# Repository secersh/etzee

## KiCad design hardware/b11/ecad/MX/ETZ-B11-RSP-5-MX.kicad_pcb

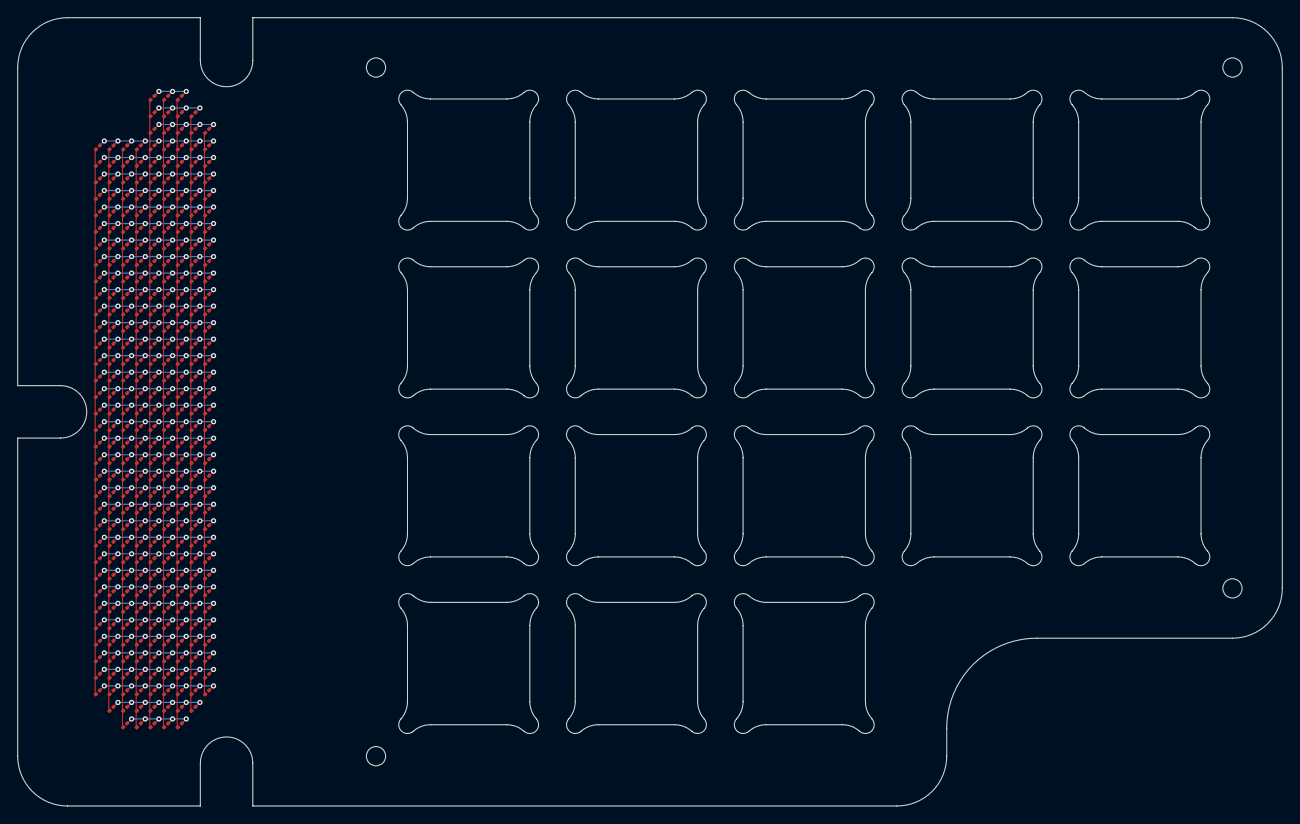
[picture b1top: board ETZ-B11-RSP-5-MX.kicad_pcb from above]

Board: 2 copper layers, 144.7 x 90.2 mm, 330 parts (0 on the bottom side), 48 nets.

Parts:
D1, D2, D3, D4, D5, D6, D7, D8, D9, D10, D11, D12, D13, D14, D15, D16, D17, D18, D19, D20, D21, D22, D23, D24, D25, D26, D27, D28, D29, D30, D31, D32, D33, D34, D35, D36, D37, D38, D39, D40, D41, D42, D43, D44, D45, D46, D47, D48, D49, D50, D51, D52, D53, D54, D55, D56, D57, D58, D59, D60, D61, D62, D63, D64, D65, D66, D67, D68, D69, D70, D71, D72, D73, D74, D75, D76, D77, D78, D79, D80, D81, D82, D83, D84, D85, D86, D87, D88, D89, D90, D91, D92, D93, D94, D95, D96, D97, D98, D99, D100, D101, D102, D103, D104, D105, D106, D107, D108, D109, D110, D111, D112, D113, D114, D115, D116, D117, D118, D119, D120, D121, D122, D123, D124, D125, D126, D127, D128, D129, D130, D131, D132, D133, D134, D135, D136, D137, D138, D139, D140, D141, D142, D143, D144, D145, D146, D147, D148, D149, D150, D151, D152, D153, D154, D155, D156, D157, D158, D159, D160, D161, D162, D163, D164, D165, D166, D167, D168, D169, D170, D171, D172, D173, D174, D175, D176, D177, D178, D179, D180, D181, D182, D183, D184, D185, D186, D187, D188, D189, D190, D191, D192, D193, D194, D195, D196, D197, D198, D199, D200, D201, D202, D203, D204, D205, D206, D207, D208, D209, D210, D211, D212, D213, D214, D215, D216, D217, D218, D219, D220, D221, D222, D223, D224, D225, D226, D227, D228, D229, D230, D231, D232, D233, D234, D235, D236, D237, D238, D239, D240, D241, D242, D243, D244, D245, D246, D247, D248, D249, D250, D251, D252, D253, D254, D255, D256, D257, D258, D259, D260, D261, D262, D263, D264, D265, D266, D267, D268, D269, D270, D271, D272, D273, D274, D275, D276, D277, D278, D279, D280, D281, D282, D283, D284, D285, D286, D287, D288, D289, D290, D291, D292, D293, D294, D295, D296, D297, D298, D299, D300, D301, D302, D303, D304, D305, D306, D307, D308, D309, D310, D311, D312, D313, D314, D315, D316, D317, D318, D319, D320, D321, D322, D323, D324, D325, D326, D327, D328, D329, D330: 0201_LED

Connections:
LED_CS1: D1.1, D2.1, D3.1
LED_CS2: D4.1, D5.1, D6.1, D7.1
LED_CS3: D8.1, D9.1, D10.1, D11.1, D12.1
LED_CS4: D13.1, D14.1, D15.1, D16.1, D17.1, D18.1, D19.1, D20.1, D21.1
LED_CS5: D22.1, D23.1, D24.1, D25.1, D26.1, D27.1, D28.1, D29.1, D30.1
LED_CS6: D31.1, D32.1, D33.1, D34.1, D35.1, D36.1, D37.1, D38.1, D39.1
LED_CS7: D40.1, D41.1, D42.1, D43.1, D44.1, D45.1, D46.1, D47.1, D48.1
LED_CS8: D49.1, D50.1, D51.1, D52.1, D53.1, D54.1, D55.1, D56.1, D57.1
LED_CS9: D58.1, D59.1, D60.1, D61.1, D62.1, D63.1, D64.1, D65.1, D66.1
LED_CS10: D67.1, D68.1, D69.1, D70.1, D71.1, D72.1, D73.1, D74.1, D75.1
LED_CS11: D76.1, D77.1, D78.1, D79.1, D80.1, D81.1, D82.1, D83.1, D84.1
LED_CS12: D85.1, D86.1, D87.1, D88.1, D89.1, D90.1, D91.1, D92.1, D93.1
LED_CS13: D94.1, D95.1, D96.1, D97.1, D98.1, D99.1, D100.1, D101.1, D102.1
LED_CS14: D103.1, D104.1, D105.1, D106.1, D107.1, D108.1, D109.1, D110.1, D111.1
LED_CS15: D112.1, D113.1, D114.1, D115.1, D116.1, D117.1, D118.1, D119.1, D120.1
LED_CS16: D121.1, D122.1, D123.1, D124.1, D125.1, D126.1, D127.1, D128.1, D129.1
LED_CS17: D130.1, D131.1, D132.1, D133.1, D134.1, D135.1, D136.1, D137.1, D138.1
LED_CS18: D139.1, D140.1, D141.1, D142.1, D143.1, D144.1, D145.1, D146.1, D147.1
LED_CS19: D148.1, D149.1, D150.1, D151.1, D152.1, D153.1, D154.1, D155.1, D156.1
LED_CS20: D157.1, D158.1, D159.1, D160.1, D161.1, D162.1, D163.1, D164.1, D165.1
LED_CS21: D166.1, D167.1, D168.1, D169.1, D170.1, D171.1, D172.1, D173.1, D174.1
LED_CS22: D175.1, D176.1, D177.1, D178.1, D179.1, D180.1, D181.1, D182.1, D183.1
LED_CS23: D184.1, D185.1, D186.1, D187.1, D188.1, D189.1, D190.1, D191.1, D192.1
LED_CS24: D193.1, D194.1, D195.1, D196.1, D197.1, D198.1, D199.1, D200.1, D201.1
LED_CS25: D202.1, D203.1, D204.1, D205.1, D206.1, D207.1, D208.1, D209.1, D210.1
LED_CS26: D211.1, D212.1, D213.1, D214.1, D215.1, D216.1, D217.1, D218.1, D219.1
LED_CS27: D220.1, D221.1, D222.1, D223.1, D224.1, D225.1, D226.1, D227.1, D228.1
LED_CS28: D229.1, D230.1, D231.1, D232.1, D233.1, D234.1, D235.1, D236.1, D237.1
LED_CS29: D238.1, D239.1, D240.1, D241.1, D242.1, D243.1, D244.1, D245.1, D246.1
LED_CS30: D247.1, D248.1, D249.1, D250.1, D251.1, D252.1, D253.1, D254.1, D255.1
LED_CS31: D256.1, D257.1, D258.1, D259.1, D260.1, D261.1, D262.1, D263.1, D264.1
LED_CS32: D265.1, D266.1, D267.1, D268.1, D269.1, D270.1, D271.1, D272.1, D273.1
LED_CS33: D274.1, D275.1, D276.1, D277.1, D278.1, D279.1, D280.1, D281.1, D282.1
LED_CS34: D283.1, D284.1, D285.1, D286.1, D287.1, D288.1, D289.1, D290.1, D291.1
LED_CS35: D292.1, D293.1, D294.1, D295.1, D296.1, D297.1, D298.1, D299.1, D300.1
LED_CS36: D301.1, D302.1, D303.1, D304.1, D305.1, D306.1, D307.1, D308.1, D309.1
LED_CS37: D310.1, D311.1, D312.1, D313.1, D314.1, D315.1, D316.1, D317.1, D318.1
LED_CS38: D319.1, D320.1, D321.1, D322.1, D323.1, D324.1, D325.1
LED_CS39: D326.1, D327.1, D328.1, D329.1, D330.1
LED_SW1: D13.2, D22.2, D31.2, D40.2, D49.2, D58.2, D67.2, D76.2, D85.2, D94.2, D103.2, D112.2, D121.2, D130.2, D139.2, D148.2, D157.2, D166.2, D175.2, D184.2, D193.2, D202.2, D211.2, D220.2, D229.2, D238.2, D247.2, D256.2, D265.2, D274.2, D283.2, D292.2, D301.2, D310.2
LED_SW2: D14.2, D23.2, D32.2, D41.2, D50.2, D59.2, D68.2, D77.2, D86.2, D95.2, D104.2, D113.2, D122.2, D131.2, D140.2, D149.2, D158.2, D167.2, D176.2, D185.2, D194.2, D203.2, D212.2, D221.2, D230.2, D239.2, D248.2, D257.2, D266.2, D275.2, D284.2, D293.2, D302.2, D311.2, D319.2
LED_SW3: D15.2, D24.2, D33.2, D42.2, D51.2, D60.2, D69.2, D78.2, D87.2, D96.2, D105.2, D114.2, D123.2, D132.2, D141.2, D150.2, D159.2, D168.2, D177.2, D186.2, D195.2, D204.2, D213.2, D222.2, D231.2, D240.2, D249.2, D258.2, D267.2, D276.2, D285.2, D294.2, D303.2, D312.2, D320.2, D326.2
LED_SW4: D16.2, D25.2, D34.2, D43.2, D52.2, D61.2, D70.2, D79.2, D88.2, D97.2, D106.2, D115.2, D124.2, D133.2, D142.2, D151.2, D160.2, D169.2, D178.2, D187.2, D196.2, D205.2, D214.2, D223.2, D232.2, D241.2, D250.2, D259.2, D268.2, D277.2, D286.2, D295.2, D304.2, D313.2, D321.2, D327.2
LED_SW5: D1.2, D4.2, D8.2, D17.2, D26.2, D35.2, D44.2, D53.2, D62.2, D71.2, D80.2, D89.2, D98.2, D107.2, D116.2, D125.2, D134.2, D143.2, D152.2, D161.2, D170.2, D179.2, D188.2, D197.2, D206.2, D215.2, D224.2, D233.2, D242.2, D251.2, D260.2, D269.2, D278.2, D287.2, D296.2, D305.2, D314.2, D322.2, D328.2
LED_SW6: D2.2, D5.2, D9.2, D18.2, D27.2, D36.2, D45.2, D54.2, D63.2, D72.2, D81.2, D90.2, D99.2, D108.2, D117.2, D126.2, D135.2, D144.2, D153.2, D162.2, D171.2, D180.2, D189.2, D198.2, D207.2, D216.2, D225.2, D234.2, D243.2, D252.2, D261.2, D270.2, D279.2, D288.2, D297.2, D306.2, D315.2, D323.2, D329.2
LED_SW7: D3.2, D6.2, D10.2, D19.2, D28.2, D37.2, D46.2, D55.2, D64.2, D73.2, D82.2, D91.2, D100.2, D109.2, D118.2, D127.2, D136.2, D145.2, D154.2, D163.2, D172.2, D181.2, D190.2, D199.2, D208.2, D217.2, D226.2, D235.2, D244.2, D253.2, D262.2, D271.2, D280.2, D289.2, D298.2, D307.2, D316.2, D324.2, D330.2
LED_SW8: D7.2, D11.2, D20.2, D29.2, D38.2, D47.2, D56.2, D65.2, D74.2, D83.2, D92.2, D101.2, D110.2, D119.2, D128.2, D137.2, D146.2, D155.2, D164.2, D173.2, D182.2, D191.2, D200.2, D209.2, D218.2, D227.2, D236.2, D245.2, D254.2, D263.2, D272.2, D281.2, D290.2, D299.2, D308.2, D317.2, D325.2
LED_SW9: D12.2, D21.2, D30.2, D39.2, D48.2, D57.2, D66.2, D75.2, D84.2, D93.2, D102.2, D111.2, D120.2, D129.2, D138.2, D147.2, D156.2, D165.2, D174.2, D183.2, D192.2, D201.2, D210.2, D219.2, D228.2, D237.2, D246.2, D255.2, D264.2, D273.2, D282.2, D291.2, D300.2, D309.2, D318.2

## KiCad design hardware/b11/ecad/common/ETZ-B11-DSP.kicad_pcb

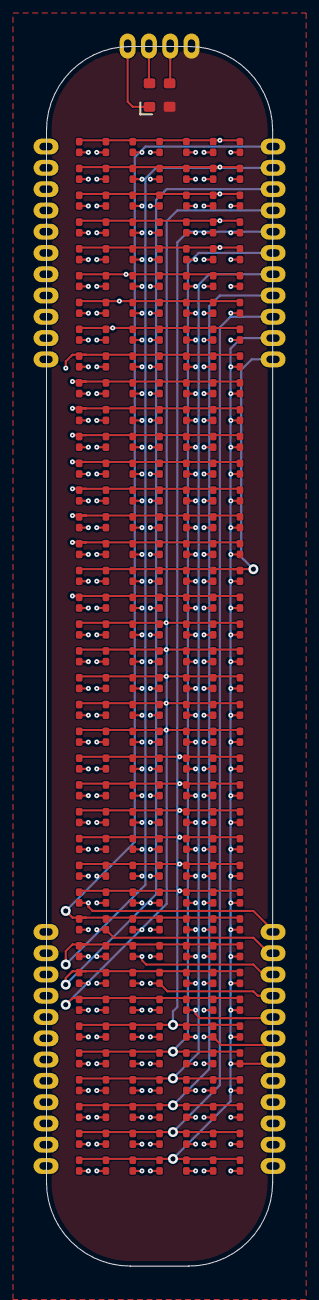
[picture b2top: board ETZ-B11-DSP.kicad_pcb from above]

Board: 4 copper layers, 13.5 x 72.8 mm, 276 parts (0 on the bottom side), 50 nets.

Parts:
D1, D2, D3, D4, D5, D6, D7, D8, D9, D10, D11, D12, D13, D14, D15, D16, D17, D18, D19, D20, D21, D22, D23, D24, D25, D26, D27, D28, D29, D30, D31, D32, D33, D34, D35, D36, D37, D38, D39, D40, D41, D42, D43, D44, D45, D46, D47, D48, D49, D50, D51, D52, D53, D54, D55, D56, D57, D58, D59, D60, D61, D62, D63, D64, D65, D66, D67, D68, D69, D70, D71, D72, D73, D74, D75, D76, D77, D78, D79, D80, D81, D82, D83, D84, D85, D86, D87, D88, D89, D90, D91, D92, D93, D94, D95, D96, D97, D98, D99, D100, D101, D102, D103, D104, D105, D106, D107, D108, D109, D110, D111, D112, D113, D114, D115, D116, D117, D118, D119, D120, D121, D122, D123, D124, D125, D126, D127, D128, D129, D130, D131, D132, D133, D134, D135, D136, D137, D138, D139, D140, D141, D142, D143, D144, D145, D146, D147, D148, D149, D150, D151, D152, D153, D154, D155, D156, D157, D158, D159, D160, D161, D162, D163, D164, D165, D166, D167, D168, D169, D170, D171, D172, D173, D174, D175, D176, D177, D178, D179, D180, D181, D182, D183, D184, D185, D186, D187, D188, D189, D190, D191, D192, D193, D194, D195, D196, D197, D198, D199, D200, D201, D202, D203, D204, D205, D206, D207, D208, D209, D210, D211, D212, D213, D214, D215, D216, D217, D218, D219, D220, D221, D222, D223, D224, D225, D226, D227, D228, D229, D230, D231, D232, D233, D234, D235, D236, D237, D238, D239, D240, D241, D242, D243, D244, D245, D246, D247, D248, D249, D250, D251, D252, D253, D254, D255, D256, D257, D258, D259, D260, D261, D262, D263, D264, D265, D266, D267, D268, D269, D270, D271, D272, D273: 0201_LED
J1: DSP_LED_CASTELLATIONS
J_ALS1: DSP_ALS_CASTELLATIONS
U_ALS1: LTR-329ALS-01

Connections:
ALS_GND: J_ALS1.4, U_ALS1.2
ALS_SCL: J_ALS1.2, U_ALS1.4
ALS_SDA: J_ALS1.3, U_ALS1.3
ALS_VDD: J_ALS1.1, U_ALS1.1
LED_CS1: D1.1, D2.1, D3.1, D4.1, D5.1, D6.1, D7.1, J1.28
LED_CS2: D8.1, D9.1, D10.1, D11.1, D12.1, D13.1, D14.1, J1.27
LED_CS3: D15.1, D16.1, D17.1, D18.1, D19.1, D20.1, D21.1, J1.26
LED_CS4: D22.1, D23.1, D24.1, D25.1, D26.1, D27.1, D28.1, J1.25
LED_CS5: D29.1, D30.1, D31.1, D32.1, D33.1, D34.1, D35.1, J1.24
LED_CS6: D36.1, D37.1, D38.1, D39.1, D40.1, D41.1, D42.1, J1.23
LED_CS7: D43.1, D44.1, D45.1, D46.1, D47.1, D48.1, D49.1, J1.22
LED_CS8: D50.1, D51.1, D52.1, D53.1, D54.1, D55.1, D56.1, J1.21
LED_CS9: D57.1, D58.1, D59.1, D60.1, D61.1, D62.1, D63.1, J1.20
LED_CS10: D64.1, D65.1, D66.1, D67.1, D68.1, D69.1, D70.1, J1.19
LED_CS11: D71.1, D72.1, D73.1, D74.1, D75.1, D76.1, D77.1, J1.18
LED_CS12: D78.1, D79.1, D80.1, D81.1, D82.1, D83.1, D84.1, J1.17
LED_CS13: D85.1, D86.1, D87.1, D88.1, D89.1, D90.1, D91.1, J1.16
LED_CS14: D92.1, D93.1, D94.1, D95.1, D96.1, D97.1, D98.1, J1.15
LED_CS15: D99.1, D100.1, D101.1, D102.1, D103.1, D104.1, D105.1, J1.14
LED_CS16: D106.1, D107.1, D108.1, D109.1, D110.1, D111.1, D112.1, J1.13
LED_CS17: D113.1, D114.1, D115.1, D116.1, D117.1, D118.1, D119.1, J1.36
LED_CS18: D120.1, D121.1, D122.1, D123.1, D124.1, D125.1, D126.1, J1.12
LED_CS19: D127.1, D128.1, D129.1, D130.1, D131.1, D132.1, D133.1, J1.11
LED_CS20: D134.1, D135.1, D136.1, D137.1, D138.1, D139.1, D140.1, J1.10
LED_CS21: D141.1, D142.1, D143.1, D144.1, D145.1, D146.1, D147.1, J1.9
LED_CS22: D148.1, D149.1, D150.1, D151.1, D152.1, D153.1, D154.1, J1.8
LED_CS23: D155.1, D156.1, D157.1, D158.1, D159.1, D160.1, D161.1, J1.7
LED_CS24: D162.1, D163.1, D164.1, D165.1, D166.1, D167.1, D168.1, J1.6
LED_CS25: D169.1, D170.1, D171.1, D172.1, D173.1, D174.1, D175.1, J1.5
LED_CS26: D176.1, D177.1, D178.1, D179.1, D180.1, D181.1, D182.1, J1.4
LED_CS27: D183.1, D184.1, D185.1, D186.1, D187.1, D188.1, D189.1, J1.3
LED_CS28: D190.1, D191.1, D192.1, D193.1, D194.1, D195.1, D196.1, J1.2
LED_CS29: D197.1, D198.1, D199.1, D200.1, D201.1, D202.1, D203.1, J1.1
LED_CS30: D204.1, D205.1, D206.1, D207.1, D208.1, D209.1, D210.1, J1.46
LED_CS31: D211.1, D212.1, D213.1, D214.1, D215.1, D216.1, D217.1, J1.45
LED_CS32: D218.1, D219.1, D220.1, D221.1, D222.1, D223.1, D224.1, J1.44
LED_CS33: D225.1, D226.1, D227.1, D228.1, D229.1, D230.1, D231.1, J1.43
LED_CS34: D232.1, D233.1, D234.1, D235.1, D236.1, D237.1, D238.1, J1.42
LED_CS35: D239.1, D240.1, D241.1, D242.1, D243.1, D244.1, D245.1, J1.41
LED_CS36: D246.1, D247.1, D248.1, D249.1, D250.1, D251.1, D252.1, J1.40
LED_CS37: D253.1, D254.1, D255.1, D256.1, D257.1, D258.1, D259.1, J1.39
LED_CS38: D260.1, D261.1, D262.1, D263.1, D264.1, D265.1, D266.1, J1.38
LED_CS39: D267.1, D268.1, D269.1, D270.1, D271.1, D272.1, D273.1, J1.37
LED_SW1: D1.2, D8.2, D15.2, D22.2, D29.2, D36.2, D43.2, D50.2, D57.2, D64.2, D71.2, D78.2, D85.2, D92.2, D99.2, D106.2, D113.2, D120.2, D127.2, D134.2, D141.2, D148.2, D155.2, D162.2, D169.2, D176.2, D183.2, D190.2, D197.2, D204.2, D211.2, D218.2, D225.2, D232.2, D239.2, D246.2, D253.2, D260.2, D267.2, J1.35
LED_SW2: D2.2, D9.2, D16.2, D23.2, D30.2, D37.2, D44.2, D51.2, D58.2, D65.2, D72.2, D79.2, D86.2, D93.2, D100.2, D107.2, D114.2, D121.2, D128.2, D135.2, D142.2, D149.2, D156.2, D163.2, D170.2, D177.2, D184.2, D191.2, D198.2, D205.2, D212.2, D219.2, D226.2, D233.2, D240.2, D247.2, D254.2, D261.2, D268.2, J1.34
LED_SW3: D3.2, D10.2, D17.2, D24.2, D31.2, D38.2, D45.2, D52.2, D59.2, D66.2, D73.2, D80.2, D87.2, D94.2, D101.2, D108.2, D115.2, D122.2, D129.2, D136.2, D143.2, D150.2, D157.2, D164.2, D171.2, D178.2, D185.2, D192.2, D199.2, D206.2, D213.2, D220.2, D227.2, D234.2, D241.2, D248.2, D255.2, D262.2, D269.2, J1.33
LED_SW4: D4.2, D11.2, D18.2, D25.2, D32.2, D39.2, D46.2, D53.2, D60.2, D67.2, D74.2, D81.2, D88.2, D95.2, D102.2, D109.2, D116.2, D123.2, D130.2, D137.2, D144.2, D151.2, D158.2, D165.2, D172.2, D179.2, D186.2, D193.2, D200.2, D207.2, D214.2, D221.2, D228.2, D235.2, D242.2, D249.2, D256.2, D263.2, D270.2, J1.32
LED_SW5: D5.2, D12.2, D19.2, D26.2, D33.2, D40.2, D47.2, D54.2, D61.2, D68.2, D75.2, D82.2, D89.2, D96.2, D103.2, D110.2, D117.2, D124.2, D131.2, D138.2, D145.2, D152.2, D159.2, D166.2, D173.2, D180.2, D187.2, D194.2, D201.2, D208.2, D215.2, D222.2, D229.2, D236.2, D243.2, D250.2, D257.2, D264.2, D271.2, J1.31
LED_SW6: D6.2, D13.2, D20.2, D27.2, D34.2, D41.2, D48.2, D55.2, D62.2, D69.2, D76.2, D83.2, D90.2, D97.2, D104.2, D111.2, D118.2, D125.2, D132.2, D139.2, D146.2, D153.2, D160.2, D167.2, D174.2, D181.2, D188.2, D195.2, D202.2, D209.2, D216.2, D223.2, D230.2, D237.2, D244.2, D251.2, D258.2, D265.2, D272.2, J1.30
LED_SW7: D7.2, D14.2, D21.2, D28.2, D35.2, D42.2, D49.2, D56.2, D63.2, D70.2, D77.2, D84.2, D91.2, D98.2, D105.2, D112.2, D119.2, D126.2, D133.2, D140.2, D147.2, D154.2, D161.2, D168.2, D175.2, D182.2, D189.2, D196.2, D203.2, D210.2, D217.2, D224.2, D231.2, D238.2, D245.2, D252.2, D259.2, D266.2, D273.2, J1.29
